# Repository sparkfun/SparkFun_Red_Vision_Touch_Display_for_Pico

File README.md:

SparkFun Red Vision Touch Display for Pico
=========================================

*[SparkFun Red Vision Touch Display for Pico](https://www.sparkfun.com/sparkfun-red-vision-touch-display-for-pico.html)*

The SparkFun Red Vision Touch Display for Pico features a 2.0", 320x240px capacative touch LCD mounted on a breakout board designed to plug directly into the Control Board on the [Experiential Robotics Platform (XRP) Kit](https://www.sparkfun.com/experiential-robotics-platform-xrp-kit.html) as well as Raspberry Pi Picos. This display board includes a connector specifically designed to allow you to plug the [SparkFun Red Vision Camera Board - HM01B0 (Color)](https://www.sparkfun.com/sparkfun-red-vision-camera-board-hm01b0-color.html) or other 2x9 connection type camera boards into the display board. Both of these boards work with the SparkFun MicroPython OpenCV port so you can add image processing, object detection, contour detection and other advanced machine vision and display features to your XRP robot. The [SparkFun Red Vision Kit for XRP](https://www.sparkfun.com/sparkfun-pico-vision-kit-for-xrp.html) contains both the display board as well as a camera board with headers for users who want to use both boards on their XRP robot with no soldering required. 

Repository Contents
-------------------

* **/Hardware** - Eagle design files (.brd, .sch)

Documentation
--------------
* **[SparkFun Red Vision MicroPython Package](https://github.com/sparkfun/red_vision/tree/main)** - MicroPython package for the SparkFun Red Vision Camera Board - HM01B0 (Color).
* **[SparkFun MicroPython OpenCV](https://github.com/sparkfun/micropython-opencv)** - MicroPython port of OpenCV code library.
* **[SparkFun MicroPython Firmware Releases](https://github.com/sparkfun/micropython/releases)** - SparkFun MicroPython firmware releases.
* **[SparkFun Red Vision Kit for XRP Hookup Guide](https://docs.sparkfun.com/SparkFun_Red_Vision_Kit_for_XRP/introduction)** - Basic hookup guide for the SparkFun Red Vision Kit for XRP (includes the Red Vision Camera Board - HM01B0).

Product Versions
----------------
* [LCD-29467](https://www.sparkfun.com/sparkfun-red-vision-touch-display-for-pico.html) - Initial release of the SparkFun Red Vision Touch Display for Pico

License Information
-------------------

This product is _**open source**_! 

Please review the LICENSE.md file for license information. 

If you have any questions or concerns on licensing, please contact technical support on our [SparkFun forums](https://forum.sparkfun.com/viewforum.php?f=152).

Distributed as-is; no warranty is given.

- Your friends at SparkFun.

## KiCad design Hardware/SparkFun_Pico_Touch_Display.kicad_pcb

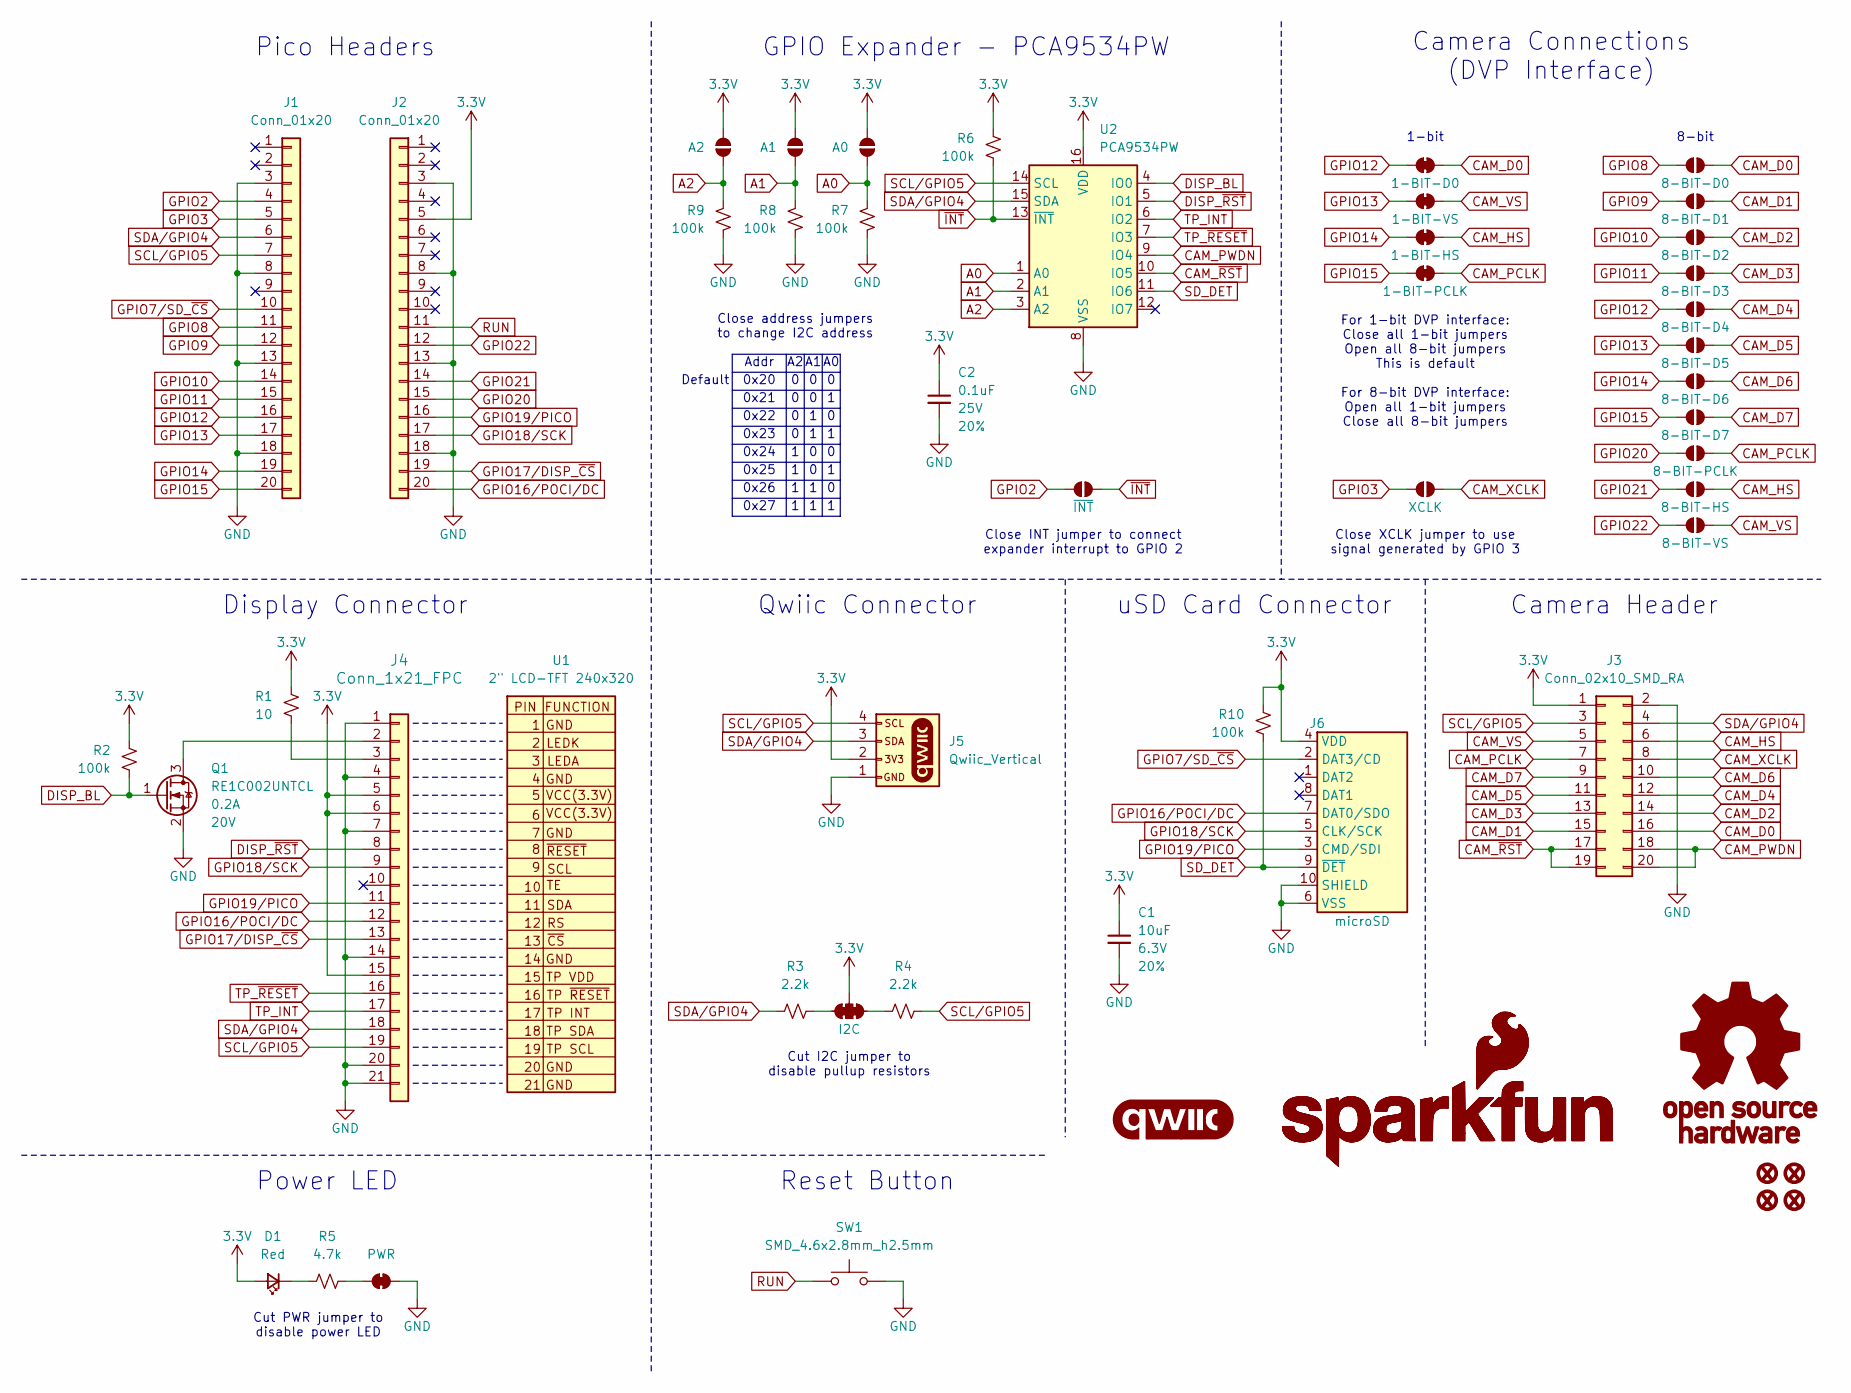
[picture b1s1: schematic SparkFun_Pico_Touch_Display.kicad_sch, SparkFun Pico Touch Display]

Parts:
C1: 10uF; C_0603_1608Metric; Voltage 6.3V; Tolerance 20%
C2: 0.1uF; C_0603_1608Metric; Voltage 25V; Tolerance 20%
D1: Red; LED_0603_1608Metric_Red
FID1, FID2, FID3, FID4: Fiducial_0.5mm; Fiducial_0.5mm_Mask1mm
G1: SparkFun_Logo; SparkFun_Logo_8mm
G2: SparkFun_Logo
G3: OSHW_Logo; Creative_Commons_License
G4: qwiic_Logo
J1, J2: Conn_01x20; 1x20_SMD_Pin1RightUp
J3: Conn_02x10_SMD_RA; 2x10_SMD_RA
J4: Conn_1x21_FPC; CONN21_FH35C-21S_HIR
J5: Qwiic_Vertical; JST_SMD_1.0mm-4_Vertical_Black
J6: microSD; microSD_External_Pin
JP1: I2C; Jumper_3_NC-2_Trace
JP2: 8-BIT-D0; Jumper_2_NO
JP3: 8-BIT-VS; Jumper_2_NO
JP4: 8-BIT-HS; Jumper_2_NO
JP5: 8-BIT-PCLK; Jumper_2_NO
JP6: 8-BIT-D3; Jumper_2_NO
JP7: 8-BIT-D2; Jumper_2_NO
JP8: 8-BIT-D1; Jumper_2_NO
JP9: 8-BIT-D4; Jumper_2_NO
JP10: 8-BIT-D5; Jumper_2_NO
JP11: 8-BIT-D6; Jumper_2_NO
JP12: 8-BIT-D7; Jumper_2_NO
JP13: XCLK; Jumper_2_NO
JP14: A0; Jumper_2_NO
JP15: A1; Jumper_2_NO
JP16: A2; Jumper_2_NO
JP17: 1-BIT-PCLK; Jumper_2_NC_Trace
JP18: 1-BIT-HS; Jumper_2_NC_Trace
JP19: 1-BIT-VS; Jumper_2_NC_Trace
JP20: 1-BIT-D0; Jumper_2_NC_Trace
JP21: PWR; Jumper_2_NC_Trace
JP22: ~{INT}; Jumper_2_NO
Q1: RE1C002UNTCL; SC-89 SOT-490
R1: 10; R_0603_1608Metric
R2, R6, R7, R8, R9, R10: 100k; R_0603_1608Metric
R3, R4: 2.2k; R_0603_1608Metric
R5: 4.7k; R_0603_1608Metric
SW1: SMD_4.6x2.8mm_h2.5mm; Push_SMD_4.6x2.8mm_h2.5mm
U1: 2" LCD-TFT 240x320; Waveshare_2_Inch_Outline
U2: PCA9534PW; TSSOP-16_4.4x5mm_P0.65mm

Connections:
3.3V: C1.1, C2.1, D1.2 (A), J2.5, J3.1, J4.5, J4.6, J4.15, J5.2, J6.4 (VDD), JP1.2 (B), JP14.2 (B), JP15.2 (B), JP16.2 (B), R1.2, R2.2, R6.2, R10.2, U2.16 (VDD)
A0: JP14.1 (A), R7.2, U2.1 (A0)
A1: JP15.1 (A), R8.2, U2.2 (A1)
A2: JP16.1 (A), R9.2, U2.3 (A2)
CAM_D0: J3.16, JP2.2 (B), JP20.1 (A)
CAM_D1: J3.15, JP8.1 (A)
CAM_D2: J3.14, JP7.1 (A)
CAM_D3: J3.13, JP6.1 (A)
CAM_D4: J3.12, JP9.1 (A)
CAM_D5: J3.11, JP10.1 (A)
CAM_D6: J3.10, JP11.1 (A)
CAM_D7: J3.9, JP12.1 (A)
CAM_HS: J3.6, JP4.2 (B), JP18.1 (A)
CAM_PCLK: J3.7, JP5.2 (B), JP17.1 (A)
CAM_PWDN: J3.18, J3.20, U2.9 (IO4)
CAM_VS: J3.5, JP3.2 (B), JP19.1 (A)
CAM_XCLK: J3.8, JP13.1 (A)
CAM_~RST: J3.17, J3.19, U2.10 (IO5)
DISP_BL: Q1.1 (G), R2.1, U2.4 (IO0)
DISP_~RST: J4.8, U2.5 (IO1)
GND: C1.2, C2.2, J1.3, J1.8, J1.13, J1.18, J2.3, J2.8, J2.13, J2.18, J3.2, J4.1, J4.4, J4.7, J4.14, J4.20, J4.21, J5.1, J6.6 (VSS), J6.10 (SHIELD), JP21.2 (B), Q1.2 (S), R7.1, R8.1, R9.1, SW1.2, U2.8 (VSS)
GPIO2: J1.4, JP22.2 (B)
GPIO3: J1.5, JP13.2 (B)
GPIO7/SD_~CS: J1.10, J6.2 (DAT3/CD)
GPIO8: J1.11, JP2.1 (A)
GPIO9: J1.12, JP8.2 (B)
GPIO10: J1.14, JP7.2 (B)
GPIO11: J1.15, JP6.2 (B)
GPIO12: J1.16, JP9.2 (B), JP20.2 (B)
GPIO13: J1.17, JP10.2 (B), JP19.2 (B)
GPIO14: J1.19, JP11.2 (B), JP18.2 (B)
GPIO15: J1.20, JP12.2 (B), JP17.2 (B)
GPIO16/POCI/DC: J2.20, J4.12, J6.7 (DAT0/SDO)
GPIO17/DISP_~CS: J2.19, J4.13
GPIO18/SCK: J2.17, J4.9, J6.5 (CLK/SCK)
GPIO19/PICO: J2.16, J4.11, J6.3 (CMD/SDI)
GPIO20: J2.15, JP5.1 (A)
GPIO21: J2.14, JP4.1 (A)
GPIO22: J2.12, JP3.1 (A)
unnamed: D1.1 (K), R5.2
unnamed: J4.2, Q1.3 (D)
unnamed: J4.3, R1.1
unnamed: JP1.1 (A), R4.1
unnamed: JP1.3 (C), R3.2
unnamed: JP21.1 (A), R5.1
RUN: J2.11, SW1.1
SCL/GPIO5: J1.7, J3.3, J4.19, J5.4, R4.2, U2.14 (SCL)
SDA/GPIO4: J1.6, J3.4, J4.18, J5.3, R3.1, U2.15 (SDA)
SD_DET: J6.9 (~DET), R10.1, U2.11 (IO6)
TP_INT: J4.17, U2.6 (IO2)
TP_~RESET: J4.16, U2.7 (IO3)
~INT: JP22.1 (A), R6.1, U2.13 (~INT)

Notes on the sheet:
1-bit
0x20
8-bit
Cut PWR jumper to disable power LED
0x22
0x27
0x24
GPIO Expander - PCA9534PW
Camera Connections (DVP Interface)
Close address jumpers to change I2C address
Default
Addr
Qwiic Connector
Cut I2C jumper to disable pullup resistors
Pico Headers
Camera Header
0x26
For 1-bit DVP interface: Close all 1-bit jumpers Open all 8-bit jumpers This is default For 8-bit DVP interface: Open all 1-bit jumpers Close all 8-bit jumpers
0x23
Display Connector
Close XCLK jumper to use signal generated by GPIO 3
0x21
uSD Card Connector
0x25
Power LED
Reset Button
Close INT jumper to connect expander interrupt to GPIO 2

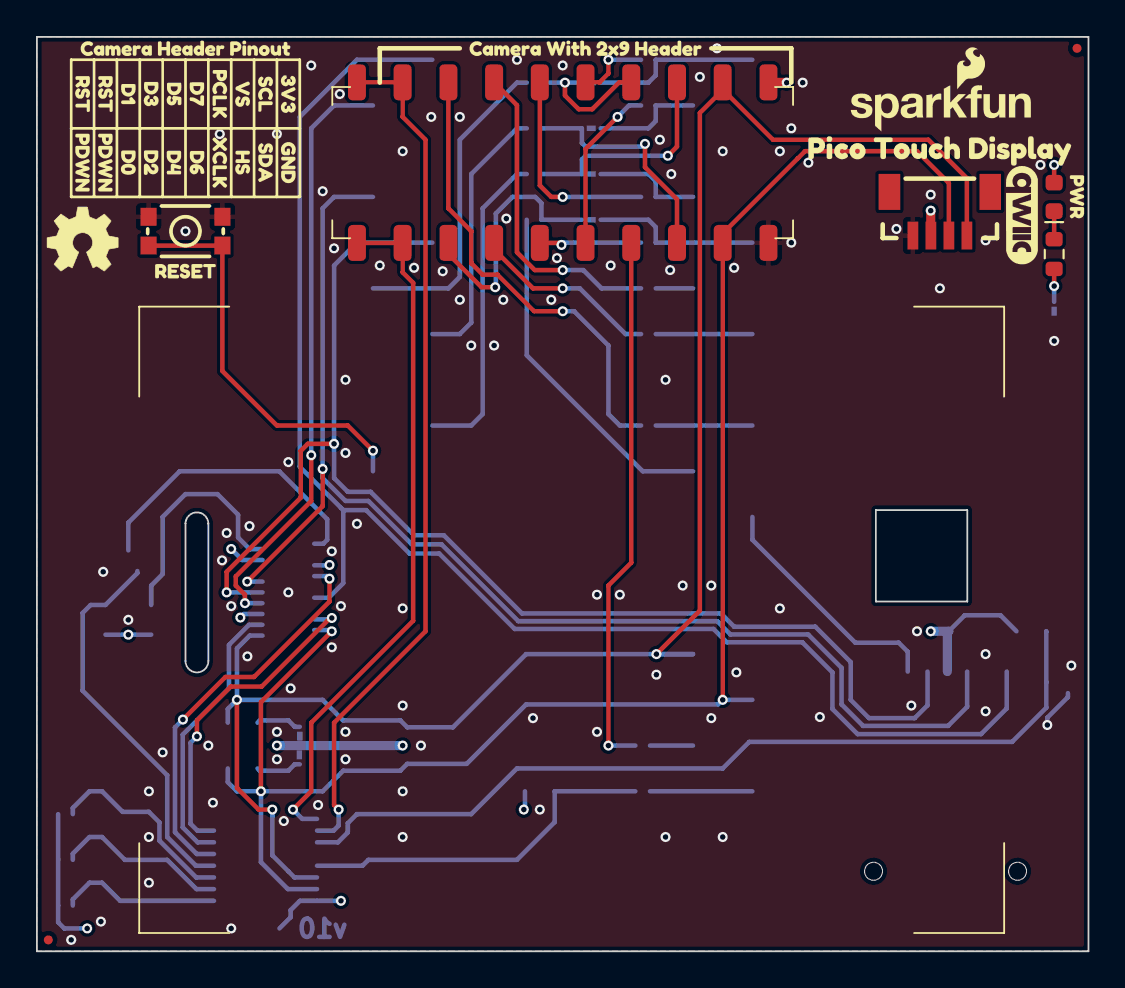
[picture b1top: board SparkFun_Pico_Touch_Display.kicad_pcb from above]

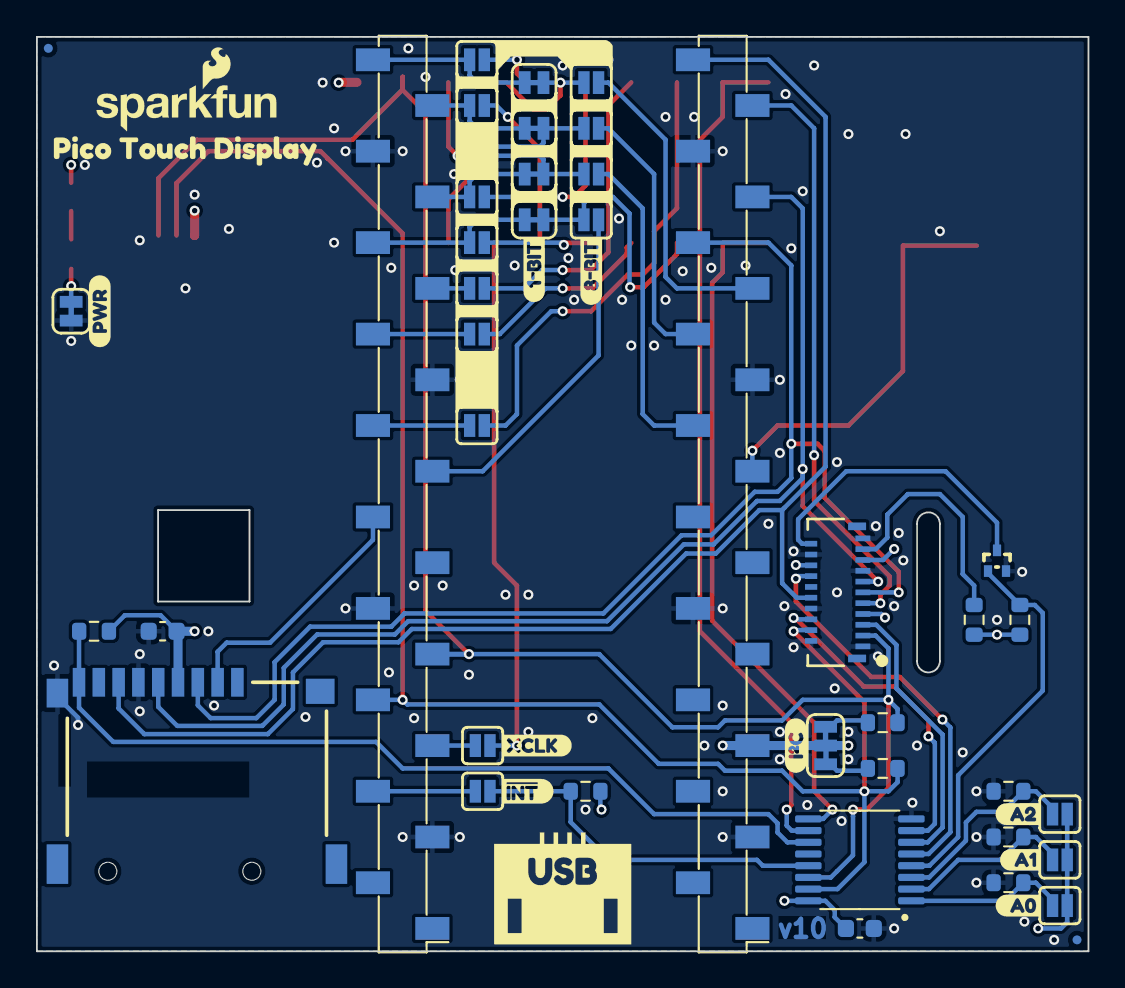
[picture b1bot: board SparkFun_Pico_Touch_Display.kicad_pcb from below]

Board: 4 copper layers, 58.4 x 50.8 mm, 87 parts (52 on the bottom side), 52 nets.

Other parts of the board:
Ref**: Val**; OSHW_Logo_4mm
kibuzzard-67A69C5F, kibuzzard-67A69C5F#2: G***; kibuzzard-67A69C5F
kibuzzard-67A69CD2, kibuzzard-67A69CD2#2: G***; kibuzzard-67A69CD2
kibuzzard-67A69CDC: G***; kibuzzard-67A69CDC
kibuzzard-67A69CE2: G***; kibuzzard-67A69CE2
kibuzzard-67A69CE6: G***; kibuzzard-67A69CE6
kibuzzard-67A69CEA: G***; kibuzzard-67A69CEA
kibuzzard-67A69CFF: G***; kibuzzard-67A69CFF
kibuzzard-67A69D0C: G***; kibuzzard-67A69D0C
kibuzzard-67A69D0F: G***; kibuzzard-67A69D0F
kibuzzard-67A69D1B: G***; kibuzzard-67A69D1B
kibuzzard-67A69D2C: G***; kibuzzard-67A69D2C
kibuzzard-67A69D2F: G***; kibuzzard-67A69D2F
kibuzzard-67A69D05: G***; kibuzzard-67A69D05
kibuzzard-67A69D16: G***; kibuzzard-67A69D16
kibuzzard-67A69D28: G***; kibuzzard-67A69D28
kibuzzard-67A69D32: G***; kibuzzard-67A69D32
kibuzzard-67A69E51: G***; kibuzzard-67A69E51
kibuzzard-67A69E55: G***; kibuzzard-67A69E55
kibuzzard-67ABB7DF: G***; kibuzzard-67ABB7DF
kibuzzard-67B3EC79, kibuzzard-67B3EC79#2: G***; kibuzzard-67B3EC79
kibuzzard-67B3EC92: G***; kibuzzard-67B3EC92
kibuzzard-67B3F617: G***; kibuzzard-67B3F617
kibuzzard-67B3FF40: G***; kibuzzard-67B3FF40
kibuzzard-67B3FF54: G***; kibuzzard-67B3FF54
kibuzzard-67B3FFE0: G***; kibuzzard-67B3FFE0
kibuzzard-67C124A5: G***; kibuzzard-67C124A5
kibuzzard-67C651AF: G***; kibuzzard-67C651AF
kibuzzard-67C1248C: G***; kibuzzard-67C1248C
kibuzzard-67C6452E: G***; kibuzzard-67C6452E
kibuzzard-67C64429: G***; kibuzzard-67C64429
kibuzzard-67C64532: G***; kibuzzard-67C64532
kibuzzard-681E5A39: G***; kibuzzard-681E5A39
kibuzzard-681E525B: G***; kibuzzard-681E525B

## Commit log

2025-02-27 Add initial design
2025-02-28 Clean up design
    Finish routing
    Add power LED
    Move all schematic elements inside frame
    Update display 3D model
    Stitch together GND pours
    Add measures
2025-02-28 Design review updates
    Rename jumpers to match silk
    Nudge traces to provide more isolation of I2C traces
    Add 10uF capacitor for uSD card
    Fix acid trap
    Rename MISO/MOSI to POCI/PICO
    Increase 3.3V trace width
2025-03-04 Design review updates
    Change to 4 layer
    Add GPIO expander for control signals
    Connect uSD detection pin
    Fix typo in company name on schematic
    Update datahseet link for 21-pin FPC connector
    Update KiCad libraries
2025-03-17 Design review updates
    Fix NC flags on headers and GPIO expander
    Change In2.Cu to 3.3V instead of GND
    Fix MOSFET datasheet link
    Move Qwiic silk
2025-03-17 Actually save board file
2025-03-17 Review updates
    Add 2x20 connector PROD_ID
    Move R6
    Swap In1.Cu and In2.Cu
2025-03-17 Add missing PROD_ID values
2025-05-07 Move display connector to bottom
    Previous location was too easy to accidentally unlatch
2025-05-07 Change GPIO expander to PCA9534
    PCA9554 has internal pull-up resistors on IO pins, whereas PCA9534 does not. The pull-up resistors were causing problems with the camera not being enabled by default, so this will ensure the camera's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
2025-05-07 Bump version number to v10
2025-05-09 Fix acid trap on PWDN pad
2025-05-09 Add silk about 2x9 camera header position
    Also nudge header down to accommodate
2025-05-09 Rename MCLK to XCLK
2025-05-09 Add pullup resistors to TP and DISP RST nets
2025-08-05 Updating hardware filenames
    Updating hardware filenames to match product name.
2025-08-05 Update README.md
    Updating readme with photos, links and short description.

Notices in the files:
parts and their libraries:
https://creativecommons.org/licenses/by-sa/4.0
Released under the Creative Commons Attribution Share-Alike 4.0 License
